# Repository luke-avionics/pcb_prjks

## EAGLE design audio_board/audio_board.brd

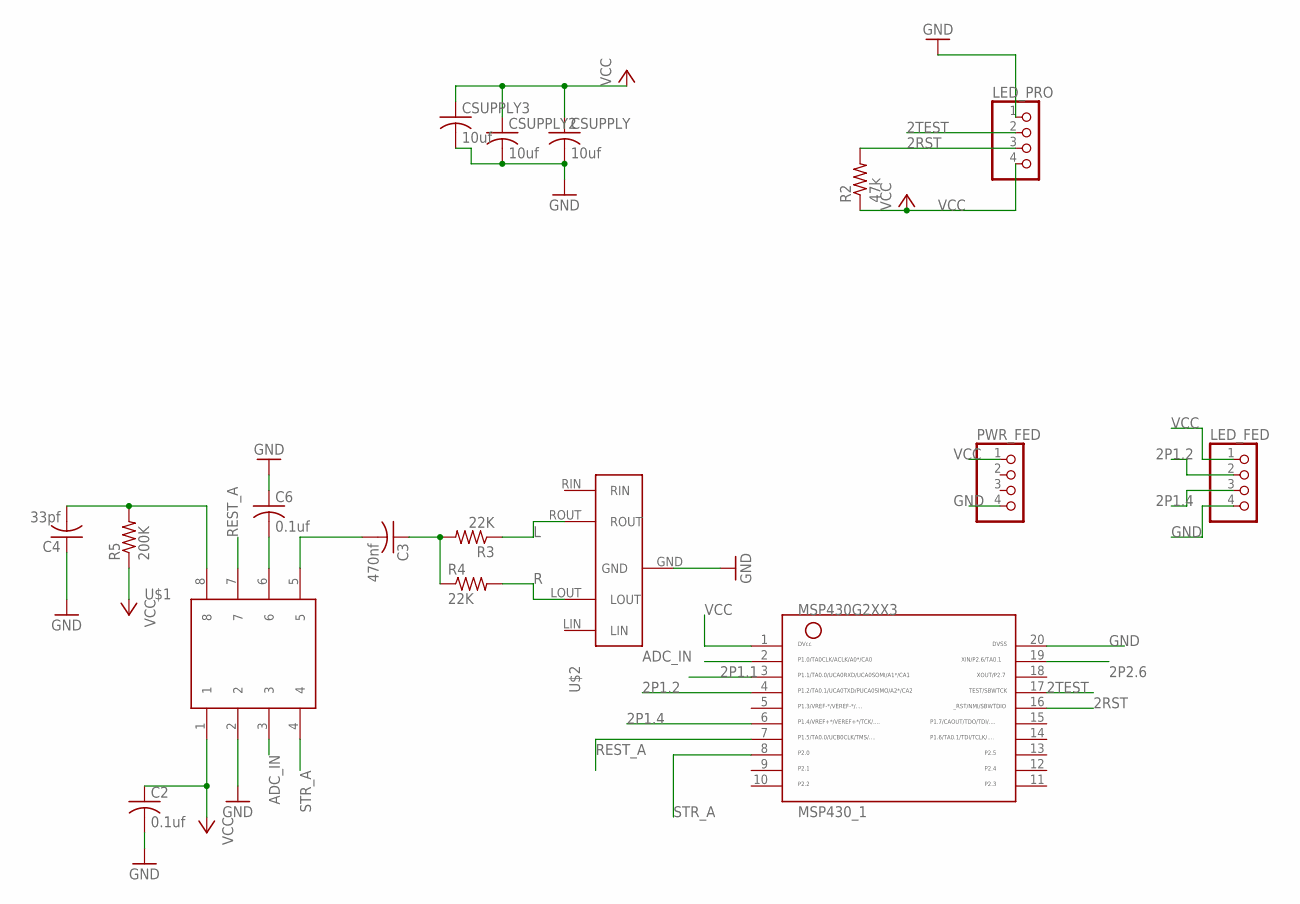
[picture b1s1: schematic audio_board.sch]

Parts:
C2, C6: 0.1uf; C1206
C3: 470nf; C1206
C4: 33pf; C1206
CSUPPLY, CSUPPLY2, CSUPPLY3: 10uf; C1206
LED_FED: PINHD-1X4; 1X04
LED_PRO: PINHD-1X4; 1X04
MSP430_1: MSP430G2XX3TSSOP; PW20
PWR_FED: PINHD-1X4; 1X04
R2: 47k; R1206
R3, R4: 22K; R1206
R5: 200K; R1206
U$1: MSGEQ7
U$2: 1699_HEAD

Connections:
2P1.1: MSP430_1.3
2P1.2: LED_FED.2, MSP430_1.4
2P1.4: LED_FED.3, MSP430_1.6
2P2.6: MSP430_1.19
2RST: LED_PRO.3, MSP430_1.16, R2.2
2TEST: LED_PRO.2, MSP430_1.17
ADC_IN: MSP430_1.2, U$1.3
GND: C2.2, C4.1, C6.1, CSUPPLY.2, CSUPPLY2.2, CSUPPLY3.2, LED_FED.4, LED_PRO.1, MSP430_1.20, PWR_FED.4, U$1.2, U$2.GND
L: R3.1, U$2.ROUT
unnamed: C3.2, U$1.5
unnamed: C3.1, R3.2, R4.1
unnamed: C6.2, U$1.6
unnamed: C4.2, R5.2, U$1.8
R: R4.2, U$2.LOUT
REST_A: MSP430_1.7, U$1.7
STR_A: MSP430_1.8, U$1.4
VCC: C2.1, CSUPPLY.1, CSUPPLY2.1, CSUPPLY3.1, LED_FED.1, LED_PRO.4, MSP430_1.1, PWR_FED.1, R2.1, R5.1, U$1.1

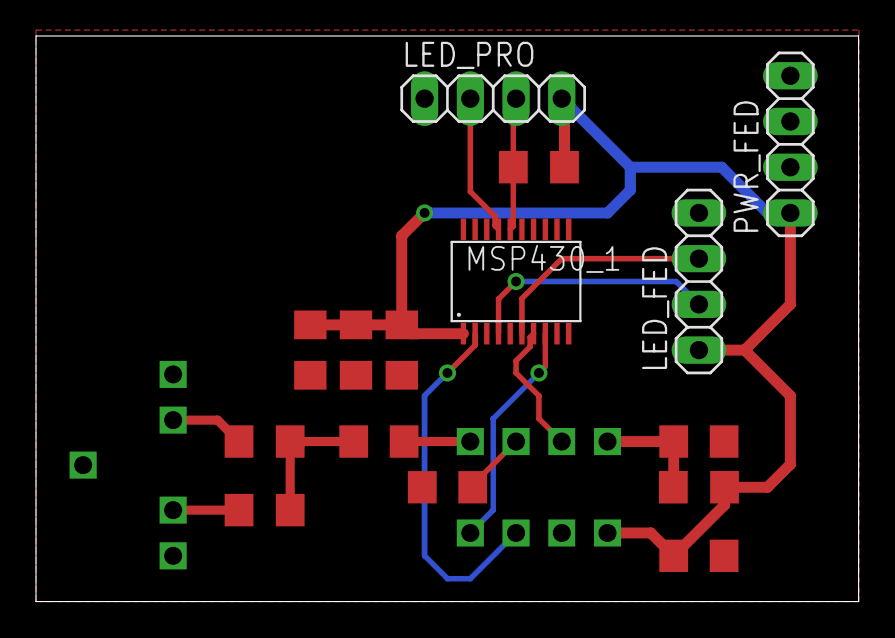
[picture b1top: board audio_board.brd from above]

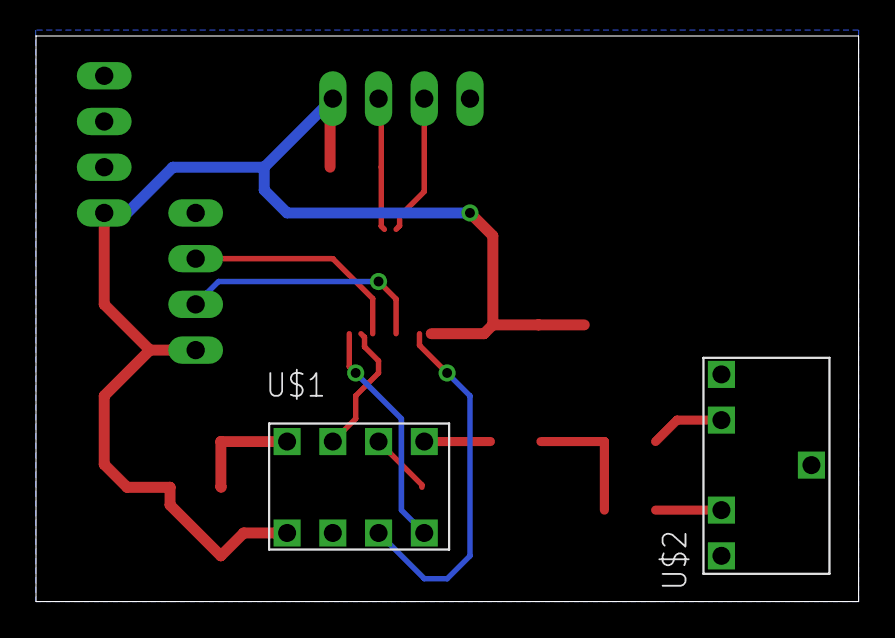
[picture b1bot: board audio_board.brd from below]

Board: 2 copper layers, 45.7 x 31.4 mm, 17 parts (2 on the bottom side), 15 nets.

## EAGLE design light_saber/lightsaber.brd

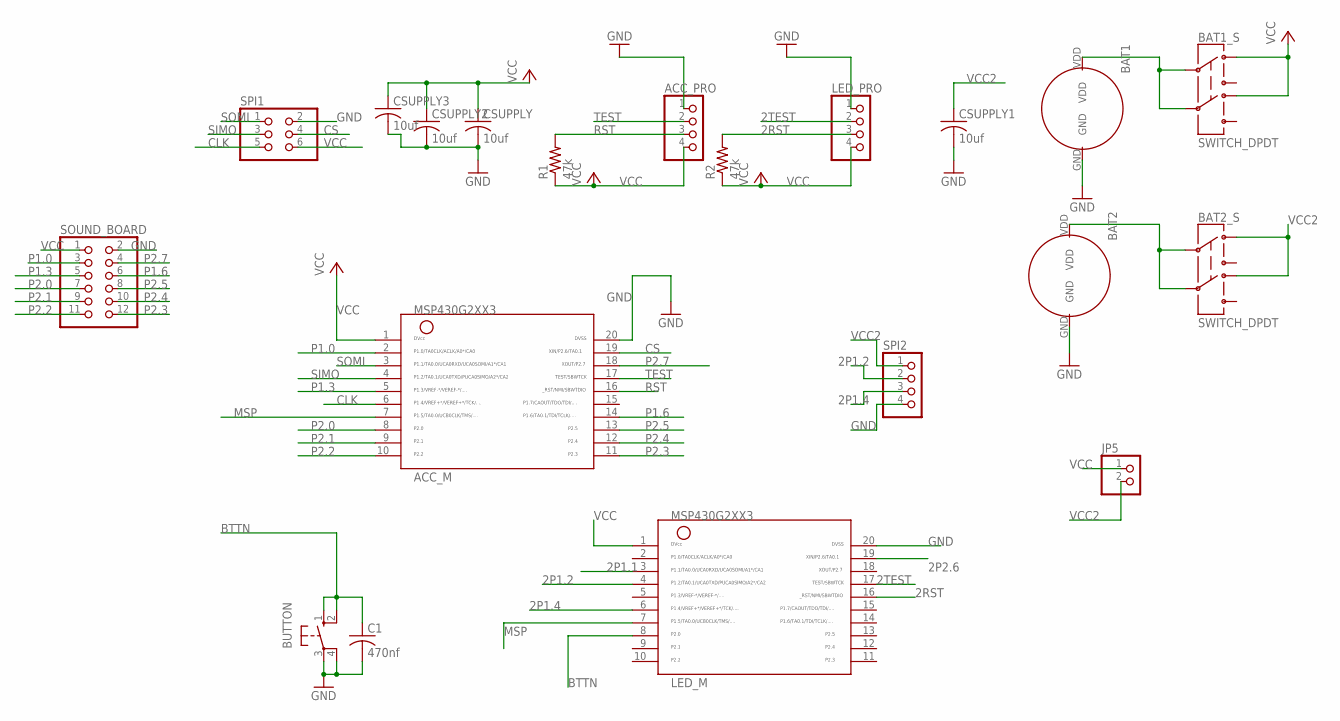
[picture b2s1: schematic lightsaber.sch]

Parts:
ACC_M: MSP430G2XX3TSSOP; PW20
ACC_PRO: PINHD-1X4; 1X04
BAT1, BAT2: BAT_PAD; BATTERY_PAD1
BAT1_S, BAT2_S: SWITCH_DPDT; JS_DPDT_TH
BUTTON: 10-XX; B3F-10XX
C1: 470nf; C1206
CSUPPLY, CSUPPLY1, CSUPPLY2, CSUPPLY3: 10uf; C1206
JP5: PINHD-1X2; 1X02
LED_M: MSP430G2XX3TSSOP; PW20
LED_PRO: PINHD-1X4; 1X04
R1, R2: 47k; R1206
SOUND_BOARD: PINHD-2X6; 2X06
SPI1: PINHD-2X3; 2X03
SPI2: PINHD-1X4; 1X04

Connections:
2P1.1: LED_M.3
2P1.2: LED_M.4, SPI2.2
2P1.4: LED_M.6, SPI2.3
2P2.6: LED_M.19
2RST: LED_M.16, LED_PRO.3, R2.2
2TEST: LED_M.17, LED_PRO.2
BAT_VCC: BAT1.VDD, BAT1_S.2, BAT1_S.5
BAT_VCC2: BAT2.VDD, BAT2_S.2, BAT2_S.5
BTTN: BUTTON.1 (S), BUTTON.2 (S1), C1.1, LED_M.8
CLK: ACC_M.6, SPI1.5
CS: ACC_M.19, SPI1.4
GND: ACC_M.20, ACC_PRO.1, BAT1.GND, BAT2.GND, BUTTON.3, BUTTON.4 (P1), C1.2, CSUPPLY.2, CSUPPLY1.2, CSUPPLY2.2, CSUPPLY3.2, LED_M.20, LED_PRO.1, SOUND_BOARD.2, SPI1.2, SPI2.4
MSP: ACC_M.7, LED_M.7
P1.0: ACC_M.2, SOUND_BOARD.3
P1.3: ACC_M.5, SOUND_BOARD.5
P1.6: ACC_M.14, SOUND_BOARD.6
P2.0: ACC_M.8, SOUND_BOARD.7
P2.1: ACC_M.9, SOUND_BOARD.9
P2.2: ACC_M.10, SOUND_BOARD.11
P2.3: ACC_M.11, SOUND_BOARD.12
P2.4: ACC_M.12, SOUND_BOARD.10
P2.5: ACC_M.13, SOUND_BOARD.8
P2.7: ACC_M.18, SOUND_BOARD.4
RST: ACC_M.16, ACC_PRO.3, R1.2
SIMO: ACC_M.4, SPI1.3
SOMI: ACC_M.3, SPI1.1
TEST: ACC_M.17, ACC_PRO.2
VCC: ACC_M.1, ACC_PRO.4, BAT1_S.1, BAT1_S.4, CSUPPLY.1, CSUPPLY2.1, CSUPPLY3.1, JP5.1, LED_M.1, LED_PRO.4, R1.1, R2.1, SOUND_BOARD.1, SPI1.6
VCC2: BAT2_S.1, BAT2_S.4, CSUPPLY1.1, JP5.2, SPI2.1

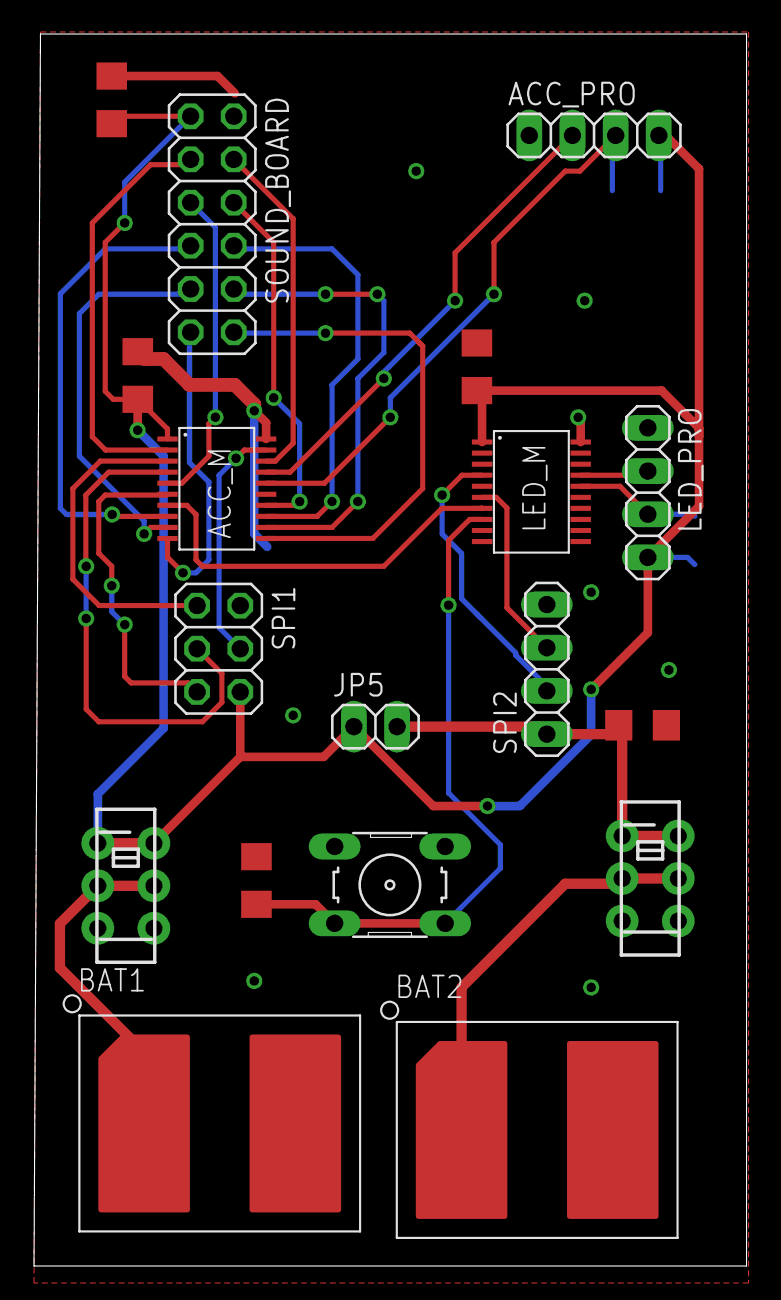
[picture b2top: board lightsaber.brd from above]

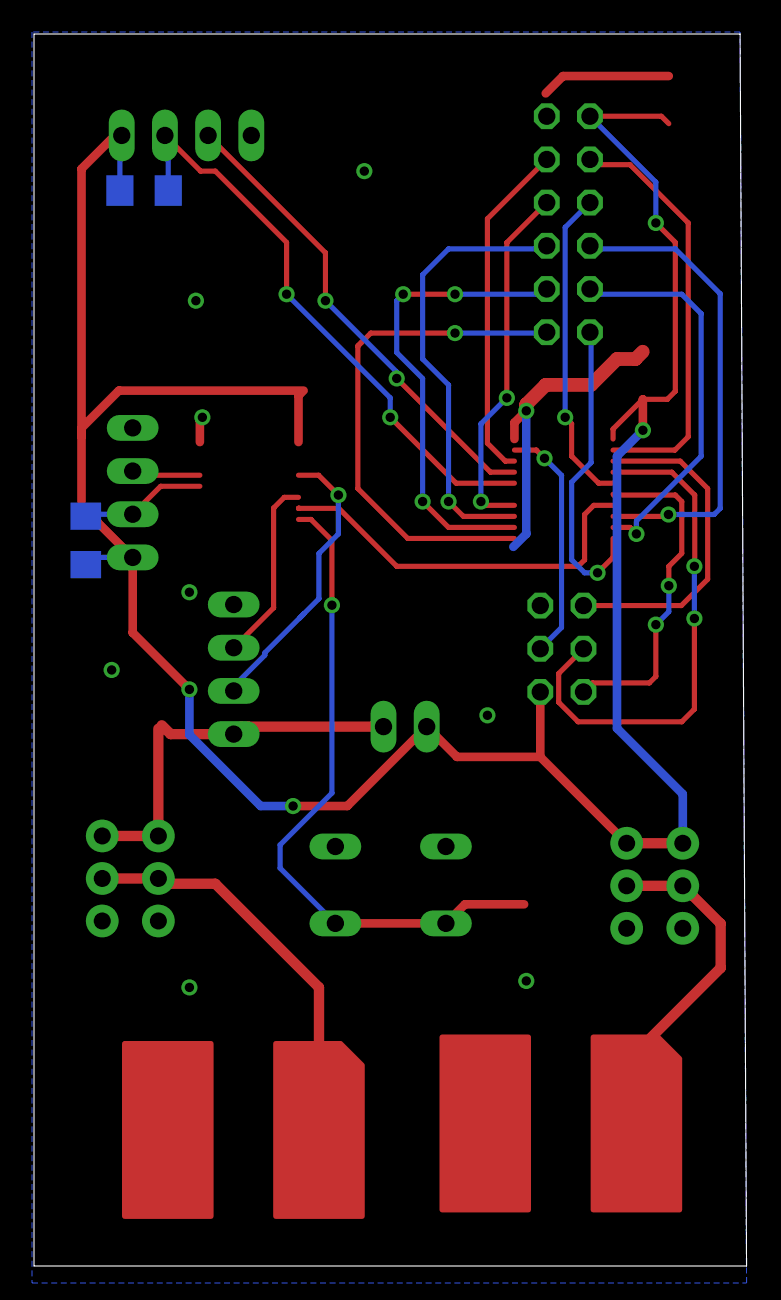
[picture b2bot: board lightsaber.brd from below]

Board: 2 copper layers, 41.9 x 72.5 mm, 20 parts (2 on the bottom side), 27 nets.

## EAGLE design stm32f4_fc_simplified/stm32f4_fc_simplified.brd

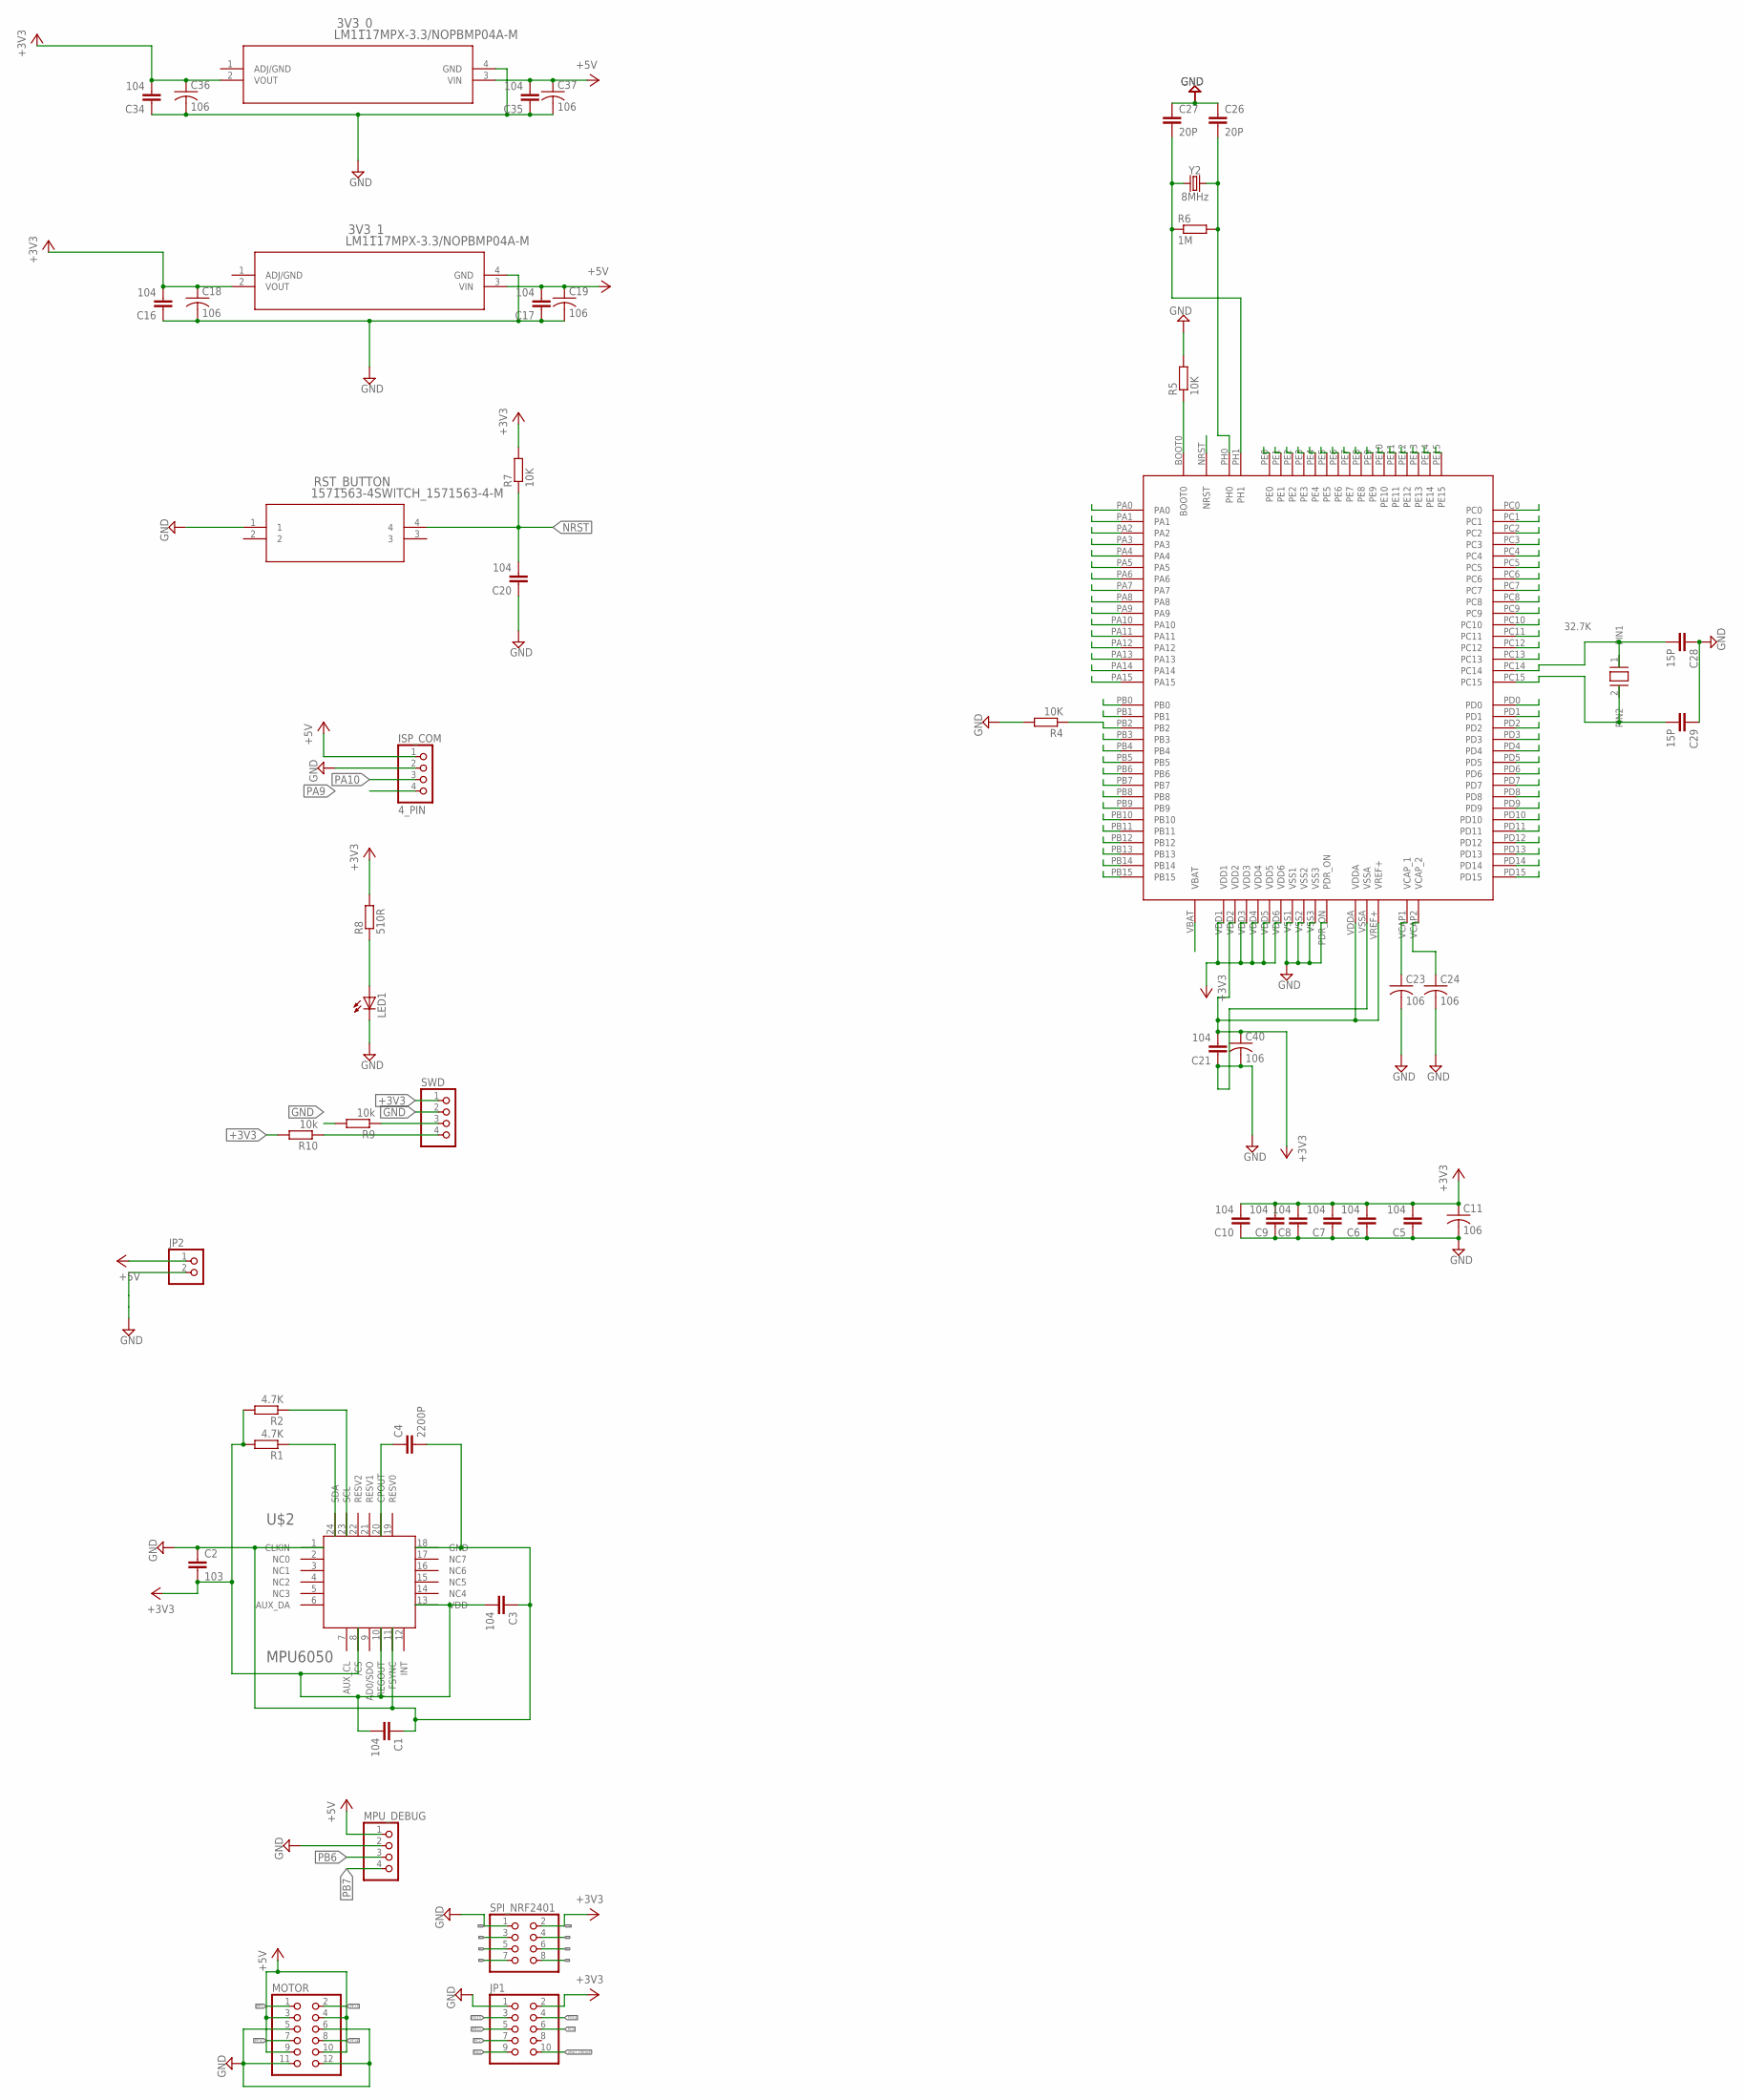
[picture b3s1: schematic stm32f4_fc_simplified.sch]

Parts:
3V3_0, 3V3_1: LM1117MPX-3.3/NOPBMP04A-M; MP04A-M
32.7K: CM315D; CM315D_32.7K
C1, C3, C5, C6, C7, C8, C9, C10, C16, C17, C20, C21, C34, C35: 104; C0603
C2: 103; C0603
C4: 2200P; C0603
C11, C18, C19, C23, C24, C36, C37, C40: 106; C0805
C26, C27: 20P; C0603
C28, C29: 15P; C0603
ISP_COM: 4_PIN; 1X04
JP1: PINHD-2X5/90; 2X05/90
JP2: PINHD-1X2; 1X02
LED1: LEDCHIPLED_0805; CHIPLED_0805
MOTOR: PINHD-2X6/90; 2X06/90
MPU_DEBUG: PINHD-1X4; 1X04
R1, R2: 4.7K; R0603
R4, R5, R7: 10K; R0603
R6: 1M; R0603
R8: 510R; R0603
R9, R10: 10k; R0603
RST_BUTTON: 1571563-4SWITCH_1571563-4-M; SWITCH_1571563-4-M
SPI_NRF2401: PINHD-2X4; 2X04
SWD: PINHD-1X4; 1X04
U$1: STM32F4V_100PIN_GENERIC; LQFP100
U$2: MPU6050
Y2: 8MHz; HC49UP

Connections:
+3V3: 3V3_0.2 (VOUT), 3V3_1.2 (VOUT), C1.2, C2.2, C3.2, C5.2, C6.2, C7.2, C8.2, C9.2, C10.2, C11.1, C16.2, C18.1, C21.2, C34.2, C36.1, C40.1, JP1.2, R1.2, R2.2, R7.2, R8.2, R10.2, SPI_NRF2401.2, SWD.1, U$1.VDD1, U$1.VDD2, U$1.VDD3, U$1.VDD4, U$1.VDD5, U$1.VDD6, U$1.VDDA, U$1.VREF+, U$2.8 (/CS), U$2.10 (REGOUT), U$2.13 (VDD)
+5V: 3V3_0.3 (VIN), 3V3_1.3 (VIN), C17.2, C19.1, C35.2, C37.1, ISP_COM.1, JP2.1, MOTOR.3, MOTOR.4, MOTOR.9, MOTOR.10, MPU_DEBUG.1
BOOT0: R5.1, U$1.BOOT0
GND: 3V3_0.4 (GND), 3V3_1.4 (GND), C1.1, C2.1, C3.1, C4.2, C5.1, C6.1, C7.1, C8.1, C9.1, C10.1, C11.2, C16.1, C17.1, C18.2, C19.2, C20.1, C21.1, C23.2, C24.2, C26.1, C27.1, C28.1, C29.1, C34.1, C35.1, C36.2, C37.2, C40.2, ISP_COM.2, JP1.1, JP2.2, LED1.C, MOTOR.5, MOTOR.6, MOTOR.11, MOTOR.12, MPU_DEBUG.2, R4.2, R5.2, R9.2, RST_BUTTON.1, SPI_NRF2401.1, SWD.2, U$1.PDR_ON, U$1.VSS1, U$1.VSS2, U$1.VSS3, U$1.VSSA, U$2.1 (CLKIN), U$2.11 (FSYNC), U$2.18 (GND)
IRQ: SPI_NRF2401.8
unnamed: LED1.A, R8.1
unnamed: C4.1, U$2.20 (CPOUT)
NRST: C20.2, R7.1, RST_BUTTON.4, U$1.NRST
PA0: JP1.9, U$1.PA0
PA1: U$1.PA1
PA2: U$1.PA2
PA3: U$1.PA3
PA4: U$1.PA4
PA5: SPI_NRF2401.5, U$1.PA5
PA6: SPI_NRF2401.7, U$1.PA6
PA7: SPI_NRF2401.6, U$1.PA7
PA8: U$1.PA8
PA9: ISP_COM.4, U$1.PA9
PA10: ISP_COM.3, U$1.PA10
PA11: U$1.PA11
PA12: U$1.PA12
PA13: R10.1, SWD.4, U$1.PA13
PA14: R9.1, SWD.3, U$1.PA14
PA15: U$1.PA15
PB0: U$1.PB0
PB1: U$1.PB1
PB2: R4.1, U$1.PB2
PB3: U$1.PB3
PB4: U$1.PB4
PB5: U$1.PB5
PB6: MPU_DEBUG.3, R2.1, U$1.PB6, U$2.23 (SCL)
PB7: MPU_DEBUG.4, R1.1, U$1.PB7, U$2.24 (SDA)
PB8: U$1.PB8
PB9: U$1.PB9
PB10: JP1.5, U$1.PB10
PB11: U$1.PB11
PB12: U$1.PB12
PB13: U$1.PB13
PB14: U$1.PB14
PB15: U$1.PB15
PC0: U$1.PC0
PC1: U$1.PC1
PC2: JP1.7, U$1.PC2
PC3: JP1.6, U$1.PC3
PC4: SPI_NRF2401.3, U$1.PC4
PC5: SPI_NRF2401.4, U$1.PC5
PC6: U$1.PC6
PC7: U$1.PC7
PC8: U$1.PC8
PC9: U$1.PC9
PC10: U$1.PC10
PC11: U$1.PC11
PC12: U$1.PC12
PC13: U$1.PC13
PC14: 32.7K.1 (PIN1), C28.2, U$1.PC14
PC15: 32.7K.2 (PIN2), C29.2, U$1.PC15
PD0: U$1.PD0
PD1: U$1.PD1
PD2: U$1.PD2
PD3: U$1.PD3
PD4: U$1.PD4
PD5: U$1.PD5
PD6: U$1.PD6
PD7: U$1.PD7
PD8: U$1.PD8
PD9: U$1.PD9
PD10: U$1.PD10
PD11: U$1.PD11
PD12: U$1.PD12
PD13: JP1.3, U$1.PD13
PD14: JP1.4, U$1.PD14
PD15: U$1.PD15
PE0: U$1.PE0
PE1: U$1.PE1
PE2: U$1.PE2
PE3: U$1.PE3
PE4: U$1.PE4
PE5: U$1.PE5
PE6: U$1.PE6
PE7: U$1.PE7
PE8: U$1.PE8
PE9: MOTOR.1, U$1.PE9
PE10: MOTOR.7, U$1.PE10
PE11: U$1.PE11
PE12: U$1.PE12
PE13: MOTOR.2, U$1.PE13
PE14: MOTOR.8, U$1.PE14
PE15: U$1.PE15
PH0: C26.2, R6.2, U$1.PH0, Y2.2
PH1: C27.2, R6.1, U$1.PH1, Y2.1
VBAT: U$1.VBAT
VBAT_DRONE: JP1.10
VCAP1: C23.1, U$1.VCAP1 (VCAP_1)
VCAP2: C24.1, U$1.VCAP2 (VCAP_2)

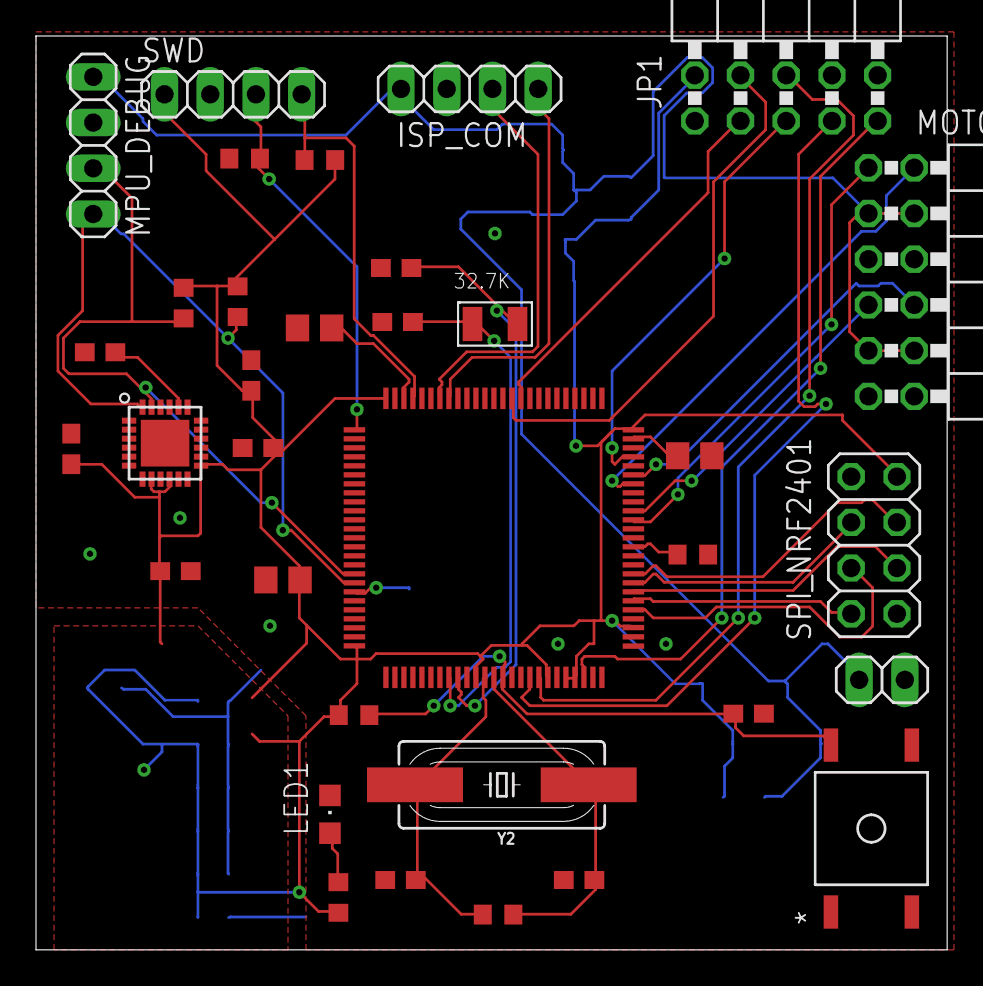
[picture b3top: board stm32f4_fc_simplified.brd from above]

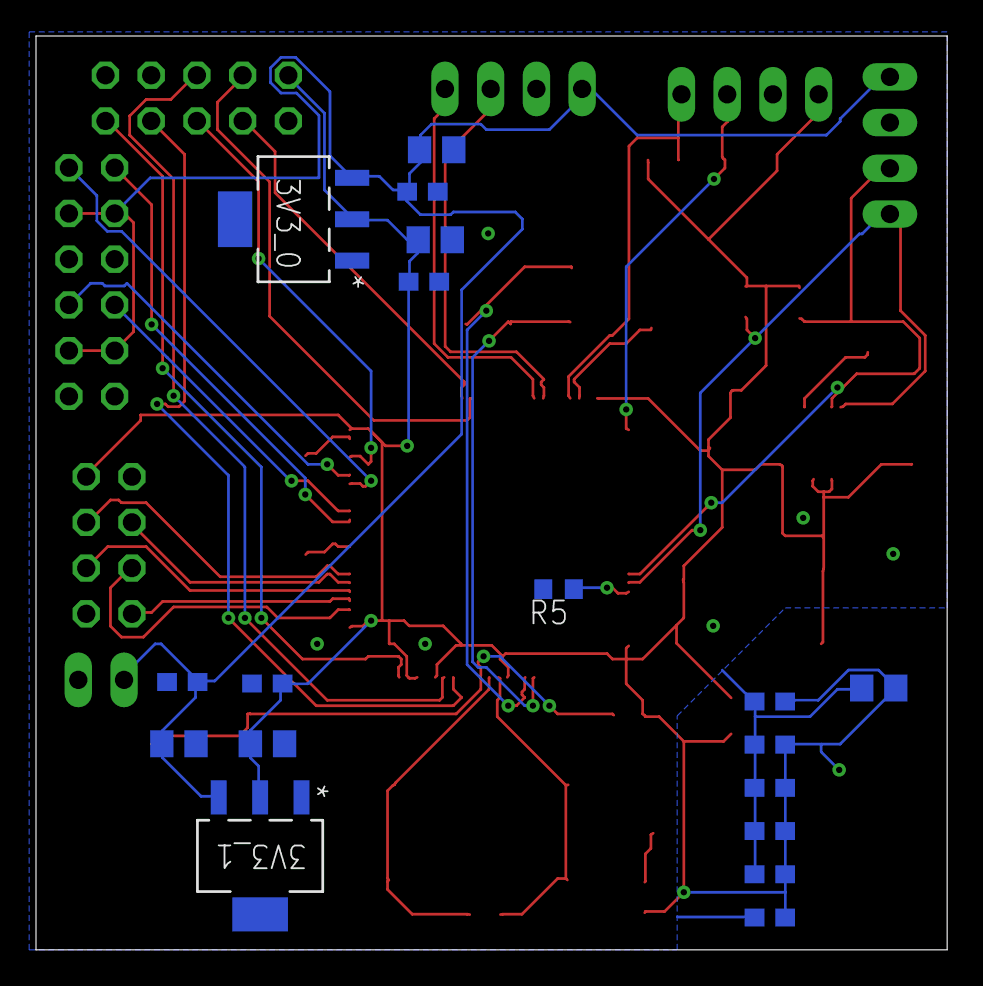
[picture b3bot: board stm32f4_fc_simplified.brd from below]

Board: 2 copper layers, 50.6 x 50.8 mm, 52 parts (18 on the bottom side), 35 nets.

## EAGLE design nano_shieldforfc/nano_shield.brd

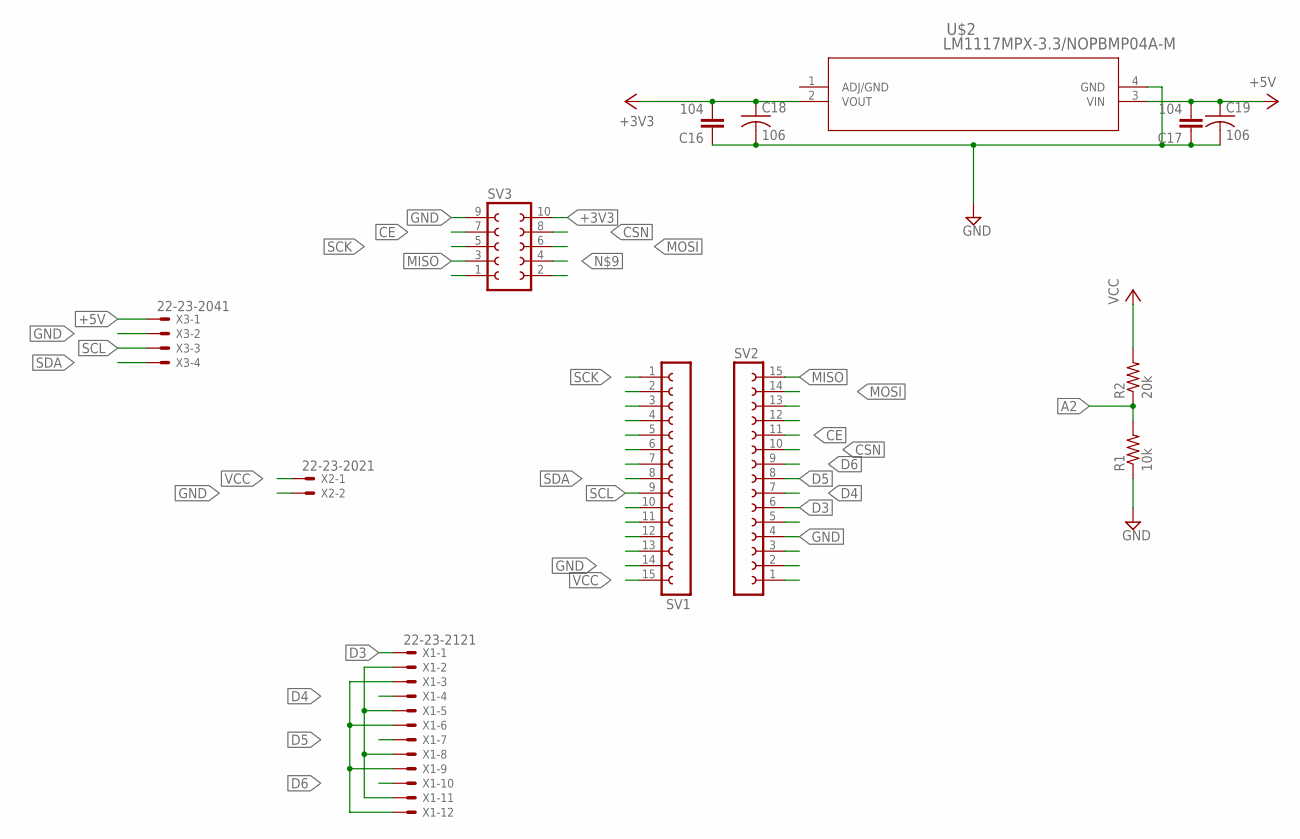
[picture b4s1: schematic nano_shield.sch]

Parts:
C16, C17: 104; C0603
C18, C19: 106; C0805
R1: 10k; R0603
R2: 20k; R0603
SV1, SV2: FE15-1; FE15
SV3: FE05-2
U$2: LM1117MPX-3.3/NOPBMP04A-M; MP04A-M
X1: 22-23-2121
X2: 22-23-2021
X3: 22-23-2041

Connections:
+3V3: C16.2, C18.1, SV3.10, U$2.2 (VOUT)
+5V: C17.2, C19.1, U$2.3 (VIN), X1.2, X1.5, X1.8, X1.11, X3.1
A2: R1.2, R2.1, SV1.6
CE: SV2.11, SV3.7
CSN: SV2.10, SV3.8
D3: SV2.6, X1.1
D4: SV2.7, X1.4
D5: SV2.8, X1.7
D6: SV2.9, X1.10
GND: C16.1, C17.1, C18.2, C19.2, R1.1, SV1.14, SV2.4, SV3.9, U$2.4 (GND), X1.3, X1.6, X1.9, X1.12, X2.2, X3.2
MISO: SV2.15, SV3.3
MOSI: SV2.14, SV3.6
SCK: SV1.1, SV3.5
SCL: SV1.9, X3.3
SDA: SV1.8, X3.4
VCC: R2.2, SV1.15, X2.1

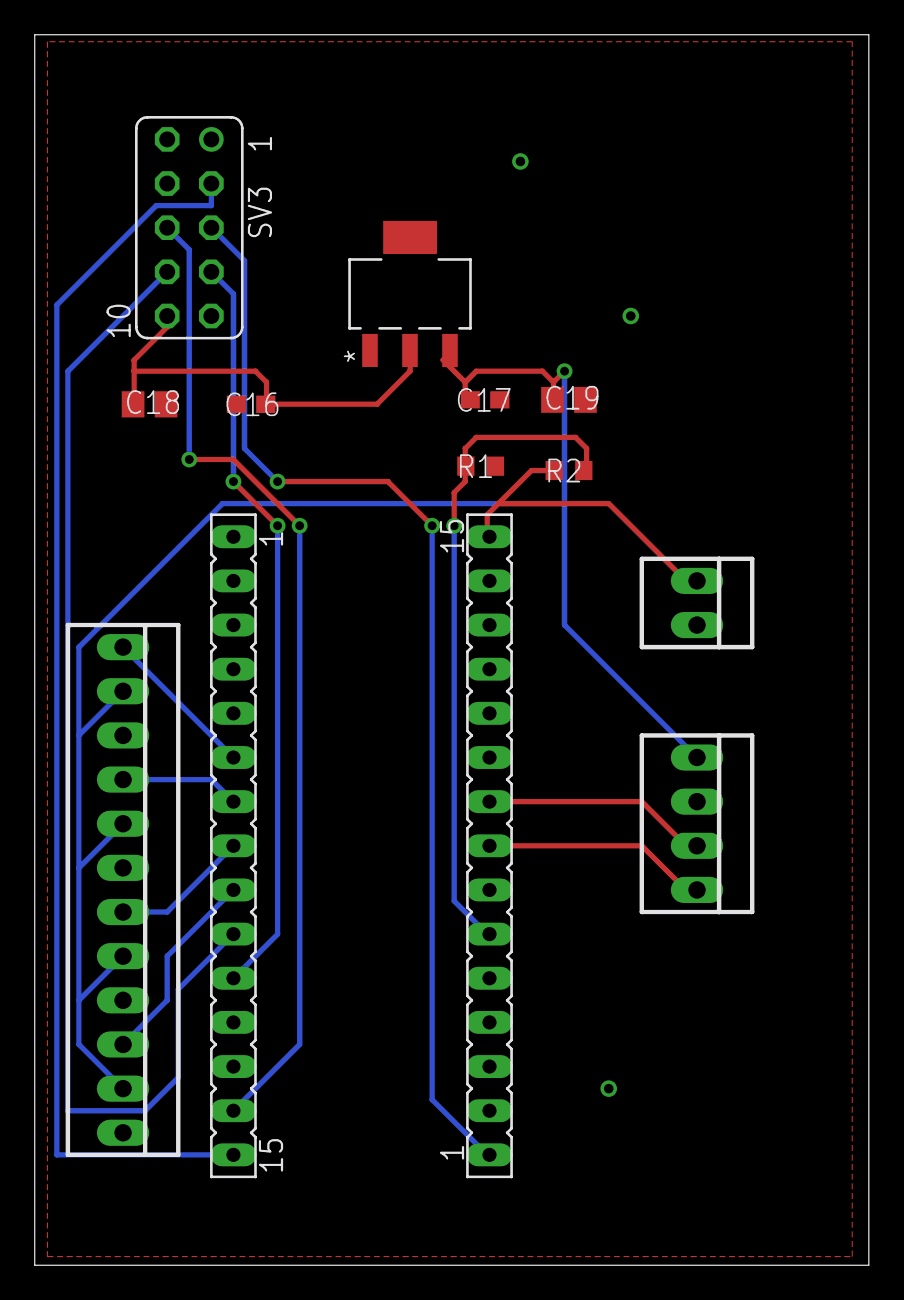
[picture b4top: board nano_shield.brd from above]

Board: 2 copper layers, 48.0 x 70.8 mm, 13 parts (0 on the bottom side), 16 nets.

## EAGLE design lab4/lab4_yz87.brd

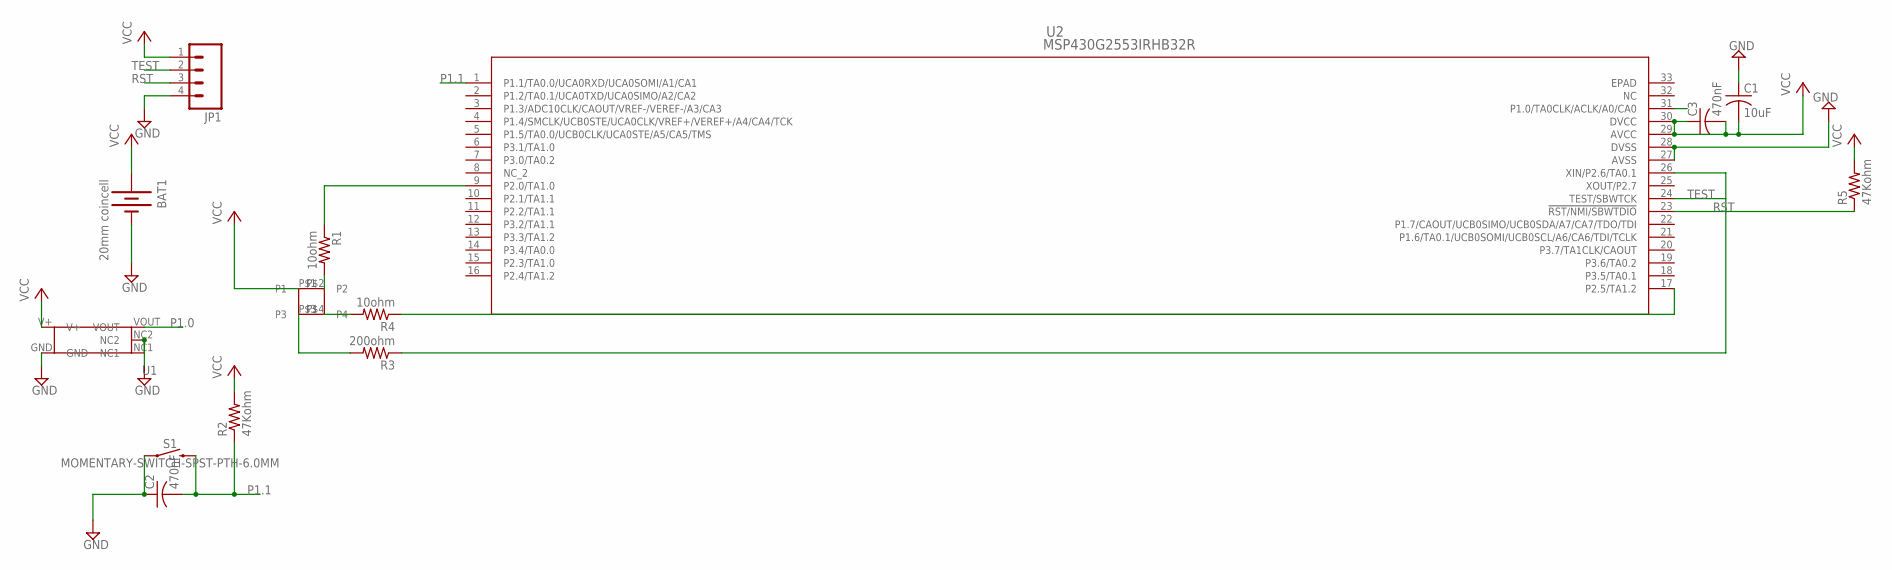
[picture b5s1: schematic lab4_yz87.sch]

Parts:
BAT1: 20mm coincell; BATTCON_20MM_PTH_COMPACT
C1: 10uF; C1206
C2, C3: 470nF; C1206
JP1: M04LOCK; 1X04_LOCK
R1, R4: 10ohm; R1206
R2, R5: 47Kohm; R1206
R3: 200ohm; R1206
S1: MOMENTARY-SWITCH-SPST-PTH-6.0MM; TACTILE_SWITCH_PTH_6.0MM
U1: TEMPERATURE_SENSOR; SOT_563
U2: MSP430G2553IRHB32R; RHB32_3P45X3P45
U$2: RGB_LED; 1210RGB

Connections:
GND: BAT1.2 (-), C1.1, C2.1, JP1.4, S1.1, U1.GND, U1.NC1, U1.NC2, U2.27 (AVSS), U2.28 (DVSS)
unnamed: R4.2, U$2.P$4 (P4)
unnamed: R1.2, U$2.P$2 (P2)
unnamed: R3.2, U$2.P$3 (P3)
unnamed: R4.1, U2.17 (P2.5/TA1.2)
unnamed: R3.1, U2.26 (XIN/P2.6/TA0.1)
unnamed: R1.1, U2.9 (P2.0/TA1.0)
P1.0: U1.VOUT, U2.31 (P1.0/TA0CLK/ACLK/A0/CA0)
P1.1: C2.2, R2.1, S1.3 (2), U2.1 (P1.1/TA0.0/UCA0RXD/UCA0SOMI/A1/CA1)
RST: JP1.3, R5.1, U2.23 (!RST/NMI/SBWTDIO)
TEST: JP1.2, U2.24 (TEST/SBWTCK)
VCC: BAT1.1 (+), BAT1.3 (+), BAT1.4 (+), BAT1.5 (+), C1.2, C3.1, C3.2, JP1.1, R2.2, R5.2, U1.V+, U2.29 (AVCC), U2.30 (DVCC), U$2.P$1 (P1)

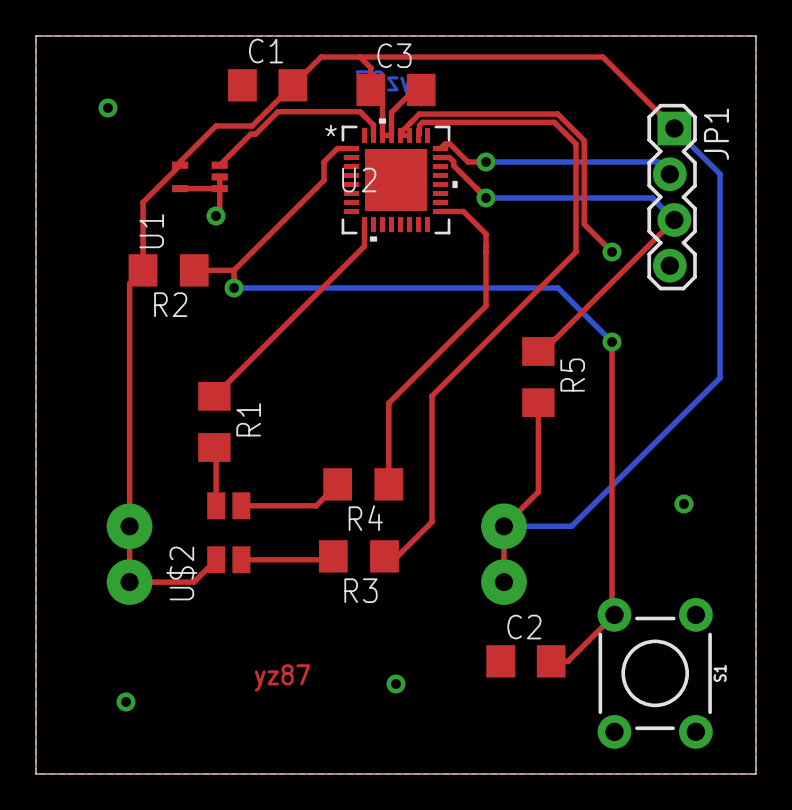
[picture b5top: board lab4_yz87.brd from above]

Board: 2 copper layers, 40.0 x 41.0 mm, 14 parts (1 on the bottom side), 12 nets.

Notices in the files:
parts and their libraries:
SparkFun-Switches: Licensing: Creative Commons ShareAlike 4.0 International - https://creativecommons.org/licenses/by-sa/4.0
SparkFun: Licensing: CC v3.0 Share-Alike You are welcome to use this library for commercial purposes.
